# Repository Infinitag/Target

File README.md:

# Infinitag Target
[![CC BY-NC-SA 4.0][cc-by-nc-sa-shield]][cc-by-nc-sa] 

The Infinitag Target is a hit target for the Infinitag system based on an ESP32 S3 module. 
The target has the following functions:

- 12 individually controllable RGBW LEDs on the front for a status display.
- IR receivers to receive the signals
- One switchable 5V connector
- One switchable 3.3V connector
- One switches to pass the incoming signal
- Power supply port
- Extension port for additional external LEDs

## Software

In the "ArduinoCode" directory is the source code as .ino file for the Arduino IDE to upload to the taget board.

### Preparation

In order for the board to be recorded successfully, you must first add another source in the settings for the board management:

```
https://dl.espressif.com/dl/package_esp32_index.json
```

The board uses the CP2102N chipset to program the ESP32.
Please check in your device management if you have installed an appropriate driver on your device.
If not, install the appropriate driver, so that the Arduino IDE recognizes the target board.

### Settings

The following must be selected as the board for the upload:
ESP32 Arduino > ESP32 S3 Dev Module

### Libraries

- esp32 by Espressif Systems v 2.0.11 (3.0.0 not working with IRremote)
- IRremote by shirriff v 4.2.0

## Hardware

### PCB

We have published all files for the PCB incl. schematic, PCB design and BOM here:

https://oshwlab.com/crusher/infinitag-target

### 3D files

The files for a 3D enclosure can be found in the folder "Hardware/3DFiles".

Additionally you can find the latest version under the following link:

https://a360.co/3NOv182

## License
This work is licensed under a
[Creative Commons Attribution-NonCommercial-ShareAlike 4.0 International License][cc-by-nc-sa].

[![CC BY-NC-SA 4.0][cc-by-nc-sa-image]][cc-by-nc-sa]

[cc-by-nc-sa]: http://creativecommons.org/licenses/by-nc-sa/4.0/
[cc-by-nc-sa-image]: https://licensebuttons.net/l/by-nc-sa/4.0/88x31.png
[cc-by-nc-sa-shield]: https://img.shields.io/badge/License-CC%20BY--NC--SA%204.0-lightgrey.svg

## Additional

For more information about the Infinitag System please visit [infinitag.io](http://www.infinitag.io).

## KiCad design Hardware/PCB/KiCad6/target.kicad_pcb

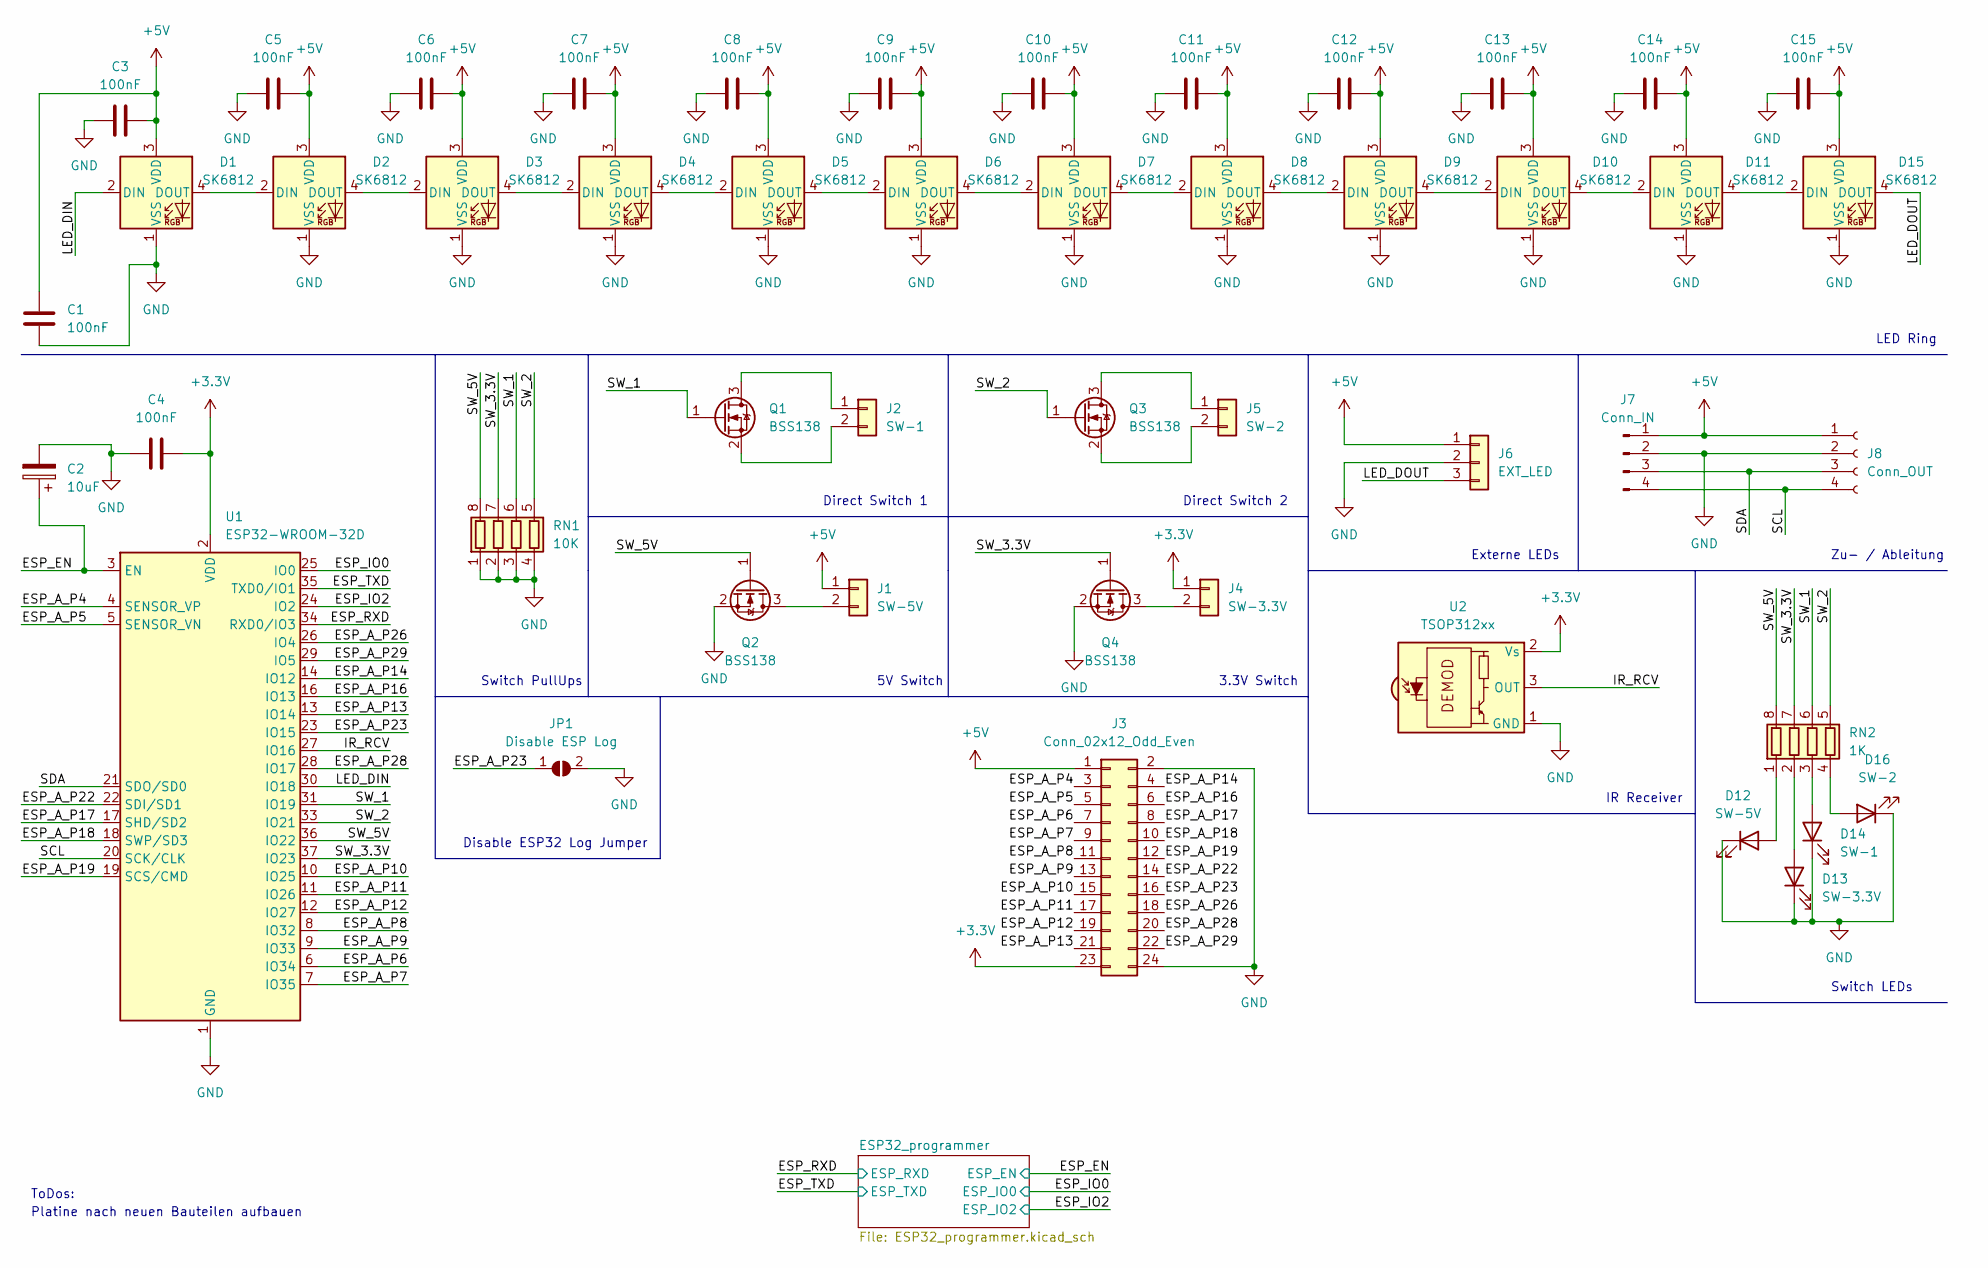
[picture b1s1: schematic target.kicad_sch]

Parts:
C1, C3, C4, C5, C6, C7, C8, C9, C10, C11, C12, C13, C14, C15: 100nF; C_0805_2012Metric_Pad1.18x1.45mm_HandSolder; LCSC C49678
C2: 10uF; CP_EIA-2012-12_Kemet-R_Pad1.30x1.05mm_HandSolder; LCSC C2976905
D1, D2, D3, D4, D5, D6, D7, D8, D9, D10, D11, D15: SK6812; LED_SK6812_PLCC4_5.0x5.0mm_P3.2mm; LCSC C5160656
D12: SW-5V; LED_1206_3216Metric_Pad1.42x1.75mm_HandSolder; LCSC C93094
D13: SW-3.3V; LED_1206_3216Metric_Pad1.42x1.75mm_HandSolder; LCSC C93094
D14: SW-1; LED_1206_3216Metric_Pad1.42x1.75mm_HandSolder; LCSC C93094
D16: SW-2; LED_1206_3216Metric_Pad1.42x1.75mm_HandSolder; LCSC C93094
J1: SW-5V; JST_PH_S2B-PH-K_1x02_P2.00mm_Horizontal; LCSC C173752
J2: SW-1; JST_PH_S2B-PH-K_1x02_P2.00mm_Horizontal; LCSC C173752
J3: Conn_02x12_Odd_Even; PinHeader_2x12_P2.54mm_Vertical; LCSC C62744
J4: SW-3.3V; JST_PH_S2B-PH-K_1x02_P2.00mm_Horizontal; LCSC C173752
J5: SW-2; JST_PH_S2B-PH-K_1x02_P2.00mm_Horizontal; LCSC C173752
J6: EXT_LED; JST_PH_S3B-PH-K_1x03_P2.00mm_Horizontal; LCSC C157929
J7: Conn_IN; JST_PH_S4B-PH-K_1x04_P2.00mm_Horizontal; LCSC C157926
J8: Conn_OUT; JST_PH_S4B-PH-K_1x04_P2.00mm_Horizontal; LCSC C157926
JP1: Disable ESP Log; SolderJumper-2_P1.3mm_Open_RoundedPad1.0x1.5mm
Q1, Q2, Q3, Q4: BSS138; SOT-23; LCSC C255592
RN1: 10K; R_Array_Convex_4x0603; LCSC C29718
RN2: 1K; R_Array_Convex_4x0603; LCSC C20197
U1: ESP32-WROOM-32D; ESP32-WROOM-32; LCSC C529578
U2: TSOP312xx; Vishay_CAST-3Pin

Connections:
+3V3: C4.2, J3.23, J4.1, U1.2 (VDD), U2.2 (Vs); also elsewhere on the board
+5V: C1.2, C3.2, C5.2, C6.2, C7.2, C8.2, C9.2, C10.2, C11.2, C12.2, C13.2, C14.2, C15.2, D1.3 (VDD), D2.3 (VDD), D3.3 (VDD), D4.3 (VDD), D5.3 (VDD), D6.3 (VDD), D7.3 (VDD), D8.3 (VDD), D9.3 (VDD), D10.3 (VDD), D11.3 (VDD), D15.3 (VDD), J1.1, J3.1, J6.1, J7.1, J8.1; also elsewhere on the board
/ESP_A_P4: J3.3, U1.4 (SENSOR_VP)
/ESP_A_P5: J3.5, U1.5 (SENSOR_VN)
/ESP_A_P6: J3.7, U1.6 (IO34)
/ESP_A_P7: J3.9, U1.7 (IO35)
/ESP_A_P8: J3.11, U1.8 (IO32)
/ESP_A_P9: J3.13, U1.9 (IO33)
/ESP_A_P10: J3.15, U1.10 (IO25)
/ESP_A_P11: J3.17, U1.11 (IO26)
/ESP_A_P12: J3.19, U1.12 (IO27)
/ESP_A_P13: J3.21, U1.13 (IO14)
/ESP_A_P14: J3.4, U1.14 (IO12)
/ESP_A_P16: J3.6, U1.16 (IO13)
/ESP_A_P17: J3.8, U1.17 (SHD/SD2)
/ESP_A_P18: J3.10, U1.18 (SWP/SD3)
/ESP_A_P19: J3.12, U1.19 (SCS/CMD)
/ESP_A_P22: J3.14, U1.22 (SDI/SD1)
/ESP_A_P23: J3.16, JP1.1 (A), U1.23 (IO15)
/ESP_A_P26: J3.18, U1.26 (IO4)
/ESP_A_P28: J3.20, U1.28 (IO17)
/ESP_A_P29: J3.22, U1.29 (IO5)
/ESP_EN: C2.1, U1.3 (EN); also elsewhere on the board
/ESP_IO0: U1.25 (IO0); also elsewhere on the board
/ESP_IO2: U1.24 (IO2); also elsewhere on the board
/ESP_RXD: U1.34 (RXD0/IO3); also elsewhere on the board
/ESP_TXD: U1.35 (TXD0/IO1); also elsewhere on the board
/IR_RCV: U1.27 (IO16), U2.3 (OUT)
/LED_DIN: D1.2 (DIN), U1.30 (IO18)
/LED_DOUT: D15.4 (DOUT), J6.3
/SCL: J7.4, J8.4, U1.20 (SCK/CLK)
/SDA: J7.3, J8.3, U1.21 (SDO/SD0)
/SW_1: Q1.1 (G), RN1.6 (R3.2), RN2.6 (R3.2), U1.31 (IO19)
/SW_2: Q3.1 (G), RN1.5 (R4.2), RN2.5 (R4.2), U1.33 (IO21)
/SW_3.3V: Q4.1 (G), RN1.7 (R2.2), RN2.7 (R2.2), U1.37 (IO23)
/SW_5V: Q2.1 (G), RN1.8 (R1.2), RN2.8 (R1.2), U1.36 (IO22)
GND: C1.1, C2.2, C3.1, C4.1, C5.1, C6.1, C7.1, C8.1, C9.1, C10.1, C11.1, C12.1, C13.1, C14.1, C15.1, D1.1 (VSS), D2.1 (VSS), D3.1 (VSS), D4.1 (VSS), D5.1 (VSS), D6.1 (VSS), D7.1 (VSS), D8.1 (VSS), D9.1 (VSS), D10.1 (VSS), D11.1 (VSS), D12.1 (K), D13.1 (K), D14.1 (K), D15.1 (VSS), D16.1 (K), J3.2, J3.24, J6.2, J7.2, J8.2, JP1.2 (B), Q2.2 (S), Q4.2 (S), RN1.1 (R1.1), RN1.2 (R2.1), RN1.3 (R3.1), RN1.4 (R4.1), U1.1 (GND), U1.15 (GND), U1.38 (GND), U1.39 (GND), U2.1 (GND); also elsewhere on the board
unnamed: D1.4 (DOUT), D2.2 (DIN)
unnamed: D2.4 (DOUT), D3.2 (DIN)
unnamed: D3.4 (DOUT), D4.2 (DIN)
unnamed: D4.4 (DOUT), D5.2 (DIN)
unnamed: D5.4 (DOUT), D6.2 (DIN)
unnamed: D6.4 (DOUT), D7.2 (DIN)
unnamed: D7.4 (DOUT), D8.2 (DIN)
unnamed: D8.4 (DOUT), D9.2 (DIN)
unnamed: D9.4 (DOUT), D10.2 (DIN)
unnamed: D10.4 (DOUT), D11.2 (DIN)
unnamed: D11.4 (DOUT), D15.2 (DIN)
unnamed: D12.2 (A), RN2.1 (R1.1)
unnamed: D13.2 (A), RN2.2 (R2.1)
unnamed: D14.2 (A), RN2.3 (R3.1)
unnamed: D16.2 (A), RN2.4 (R4.1)
unnamed: J1.2, Q2.3 (D)
unnamed: J2.1, Q1.3 (D)
unnamed: J2.2, Q1.2 (S)
unnamed: J4.2, Q4.3 (D)
unnamed: J5.1, Q3.3 (D)
unnamed: J5.2, Q3.2 (S)

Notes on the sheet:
IR Receiver
Switch LEDs
Zu- / Ableitung
ToDos:
5V Switch
LED Ring
Switch PullUps
3.3V Switch
Platine nach neuen Bauteilen aufbauen
Direct Switch 2
Externe LEDs
Direct Switch 1
Disable ESP32 Log Jumper

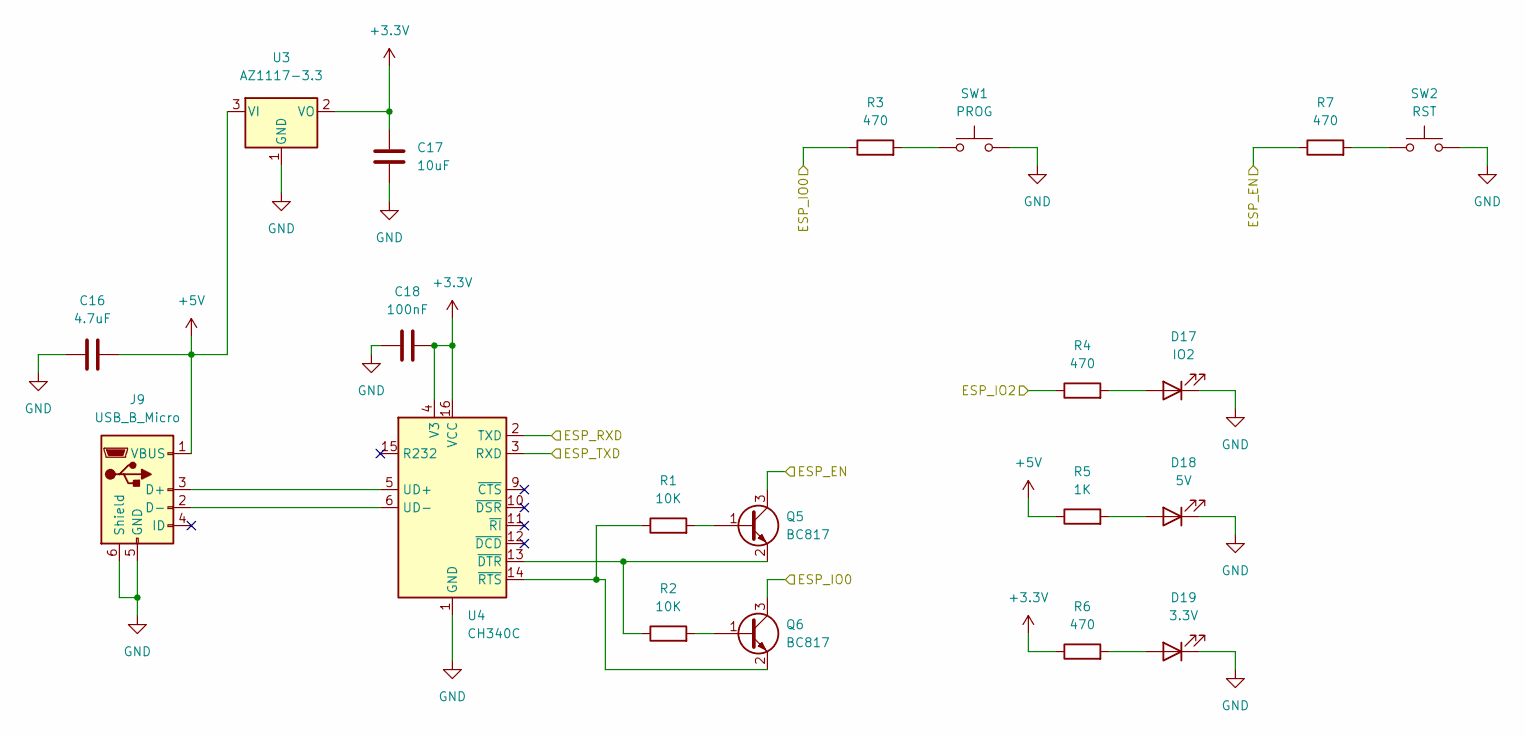
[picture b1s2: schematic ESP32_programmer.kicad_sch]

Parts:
C16: 4.7uF; C_0805_2012Metric_Pad1.18x1.45mm_HandSolder; LCSC C1779
C17: 10uF; C_0805_2012Metric_Pad1.18x1.45mm_HandSolder; LCSC C15850
C18: 100nF; C_0805_2012Metric_Pad1.18x1.45mm_HandSolder; LCSC C49678
D17: IO2; D_1206_3216Metric_Pad1.42x1.75mm_HandSolder; LCSC C88326
D18: 5V; D_1206_3216Metric_Pad1.42x1.75mm_HandSolder; LCSC C99881
D19: 3.3V; D_1206_3216Metric_Pad1.42x1.75mm_HandSolder; LCSC C99881
J9: USB_B_Micro; USB_Micro-B_Amphenol_10118194_Horizontal; LCSC C132563
Q5, Q6: BC817; SOT-23; LCSC C52801
R1, R2: 10K; R_0805_2012Metric_Pad1.20x1.40mm_HandSolder; LCSC C17414
R3, R4, R6, R7: 470; R_0805_2012Metric_Pad1.20x1.40mm_HandSolder; LCSC C17710
R5: 1K; R_0805_2012Metric_Pad1.20x1.40mm_HandSolder; LCSC C17513
SW1: PROG; SW_Push_1P1T_NO_6x6mm_H9.5mm; LCSC C83206
SW2: RST; SW_Push_1P1T_NO_6x6mm_H9.5mm; LCSC C83206
U3: AZ1117-3.3; SOT-223; LCSC C92517
U4: CH340C; SOIC-16_3.9x9.9mm_P1.27mm; LCSC C84681

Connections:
+3V3: C17.2, C18.2, R6.1, U3.2 (VO), U4.4 (V3), U4.16 (VCC); also elsewhere on the board
+5V: C16.2, J9.1 (VBUS), R5.1, U3.3 (VI); also elsewhere on the board
/ESP_EN: Q5.3 (C), R7.1; also elsewhere on the board
/ESP_IO0: Q6.3 (C), R3.1; also elsewhere on the board
/ESP_IO2: R4.1; also elsewhere on the board
/ESP_RXD: U4.2 (TXD); also elsewhere on the board
/ESP_TXD: U4.3 (RXD); also elsewhere on the board
GND: C16.1, C17.1, C18.1, D17.1 (K), D18.1 (K), D19.1 (K), J9.5 (GND), J9.6 (Shield), SW1.2, SW2.2, U3.1 (GND), U4.1 (GND); also elsewhere on the board
unnamed: D17.2 (A), R4.2
unnamed: D18.2 (A), R5.2
unnamed: D19.2 (A), R6.2
unnamed: J9.2 (D-), U4.6 (UD-)
unnamed: J9.3 (D+), U4.5 (UD+)
unnamed: Q5.1 (B), R1.2
unnamed: Q5.2 (E), R2.1, U4.13 (~DTR)
unnamed: Q6.1 (B), R2.2
unnamed: Q6.2 (E), R1.1, U4.14 (~RTS)
unnamed: R3.2, SW1.1
unnamed: R7.2, SW2.1

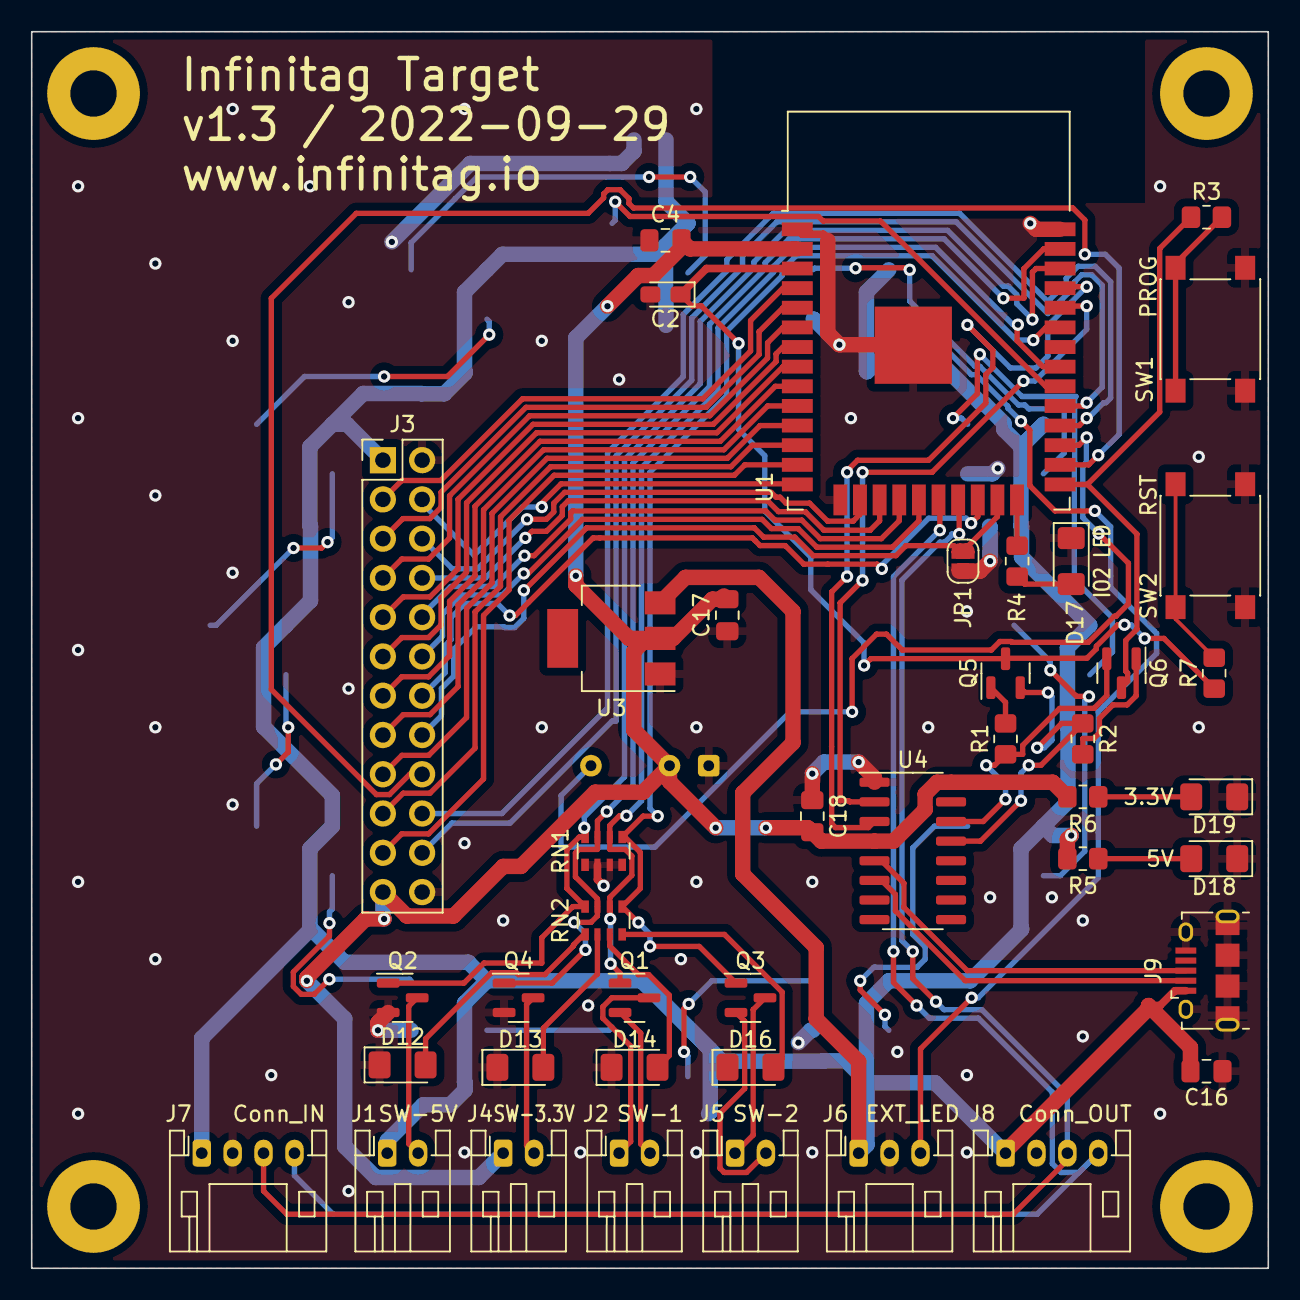
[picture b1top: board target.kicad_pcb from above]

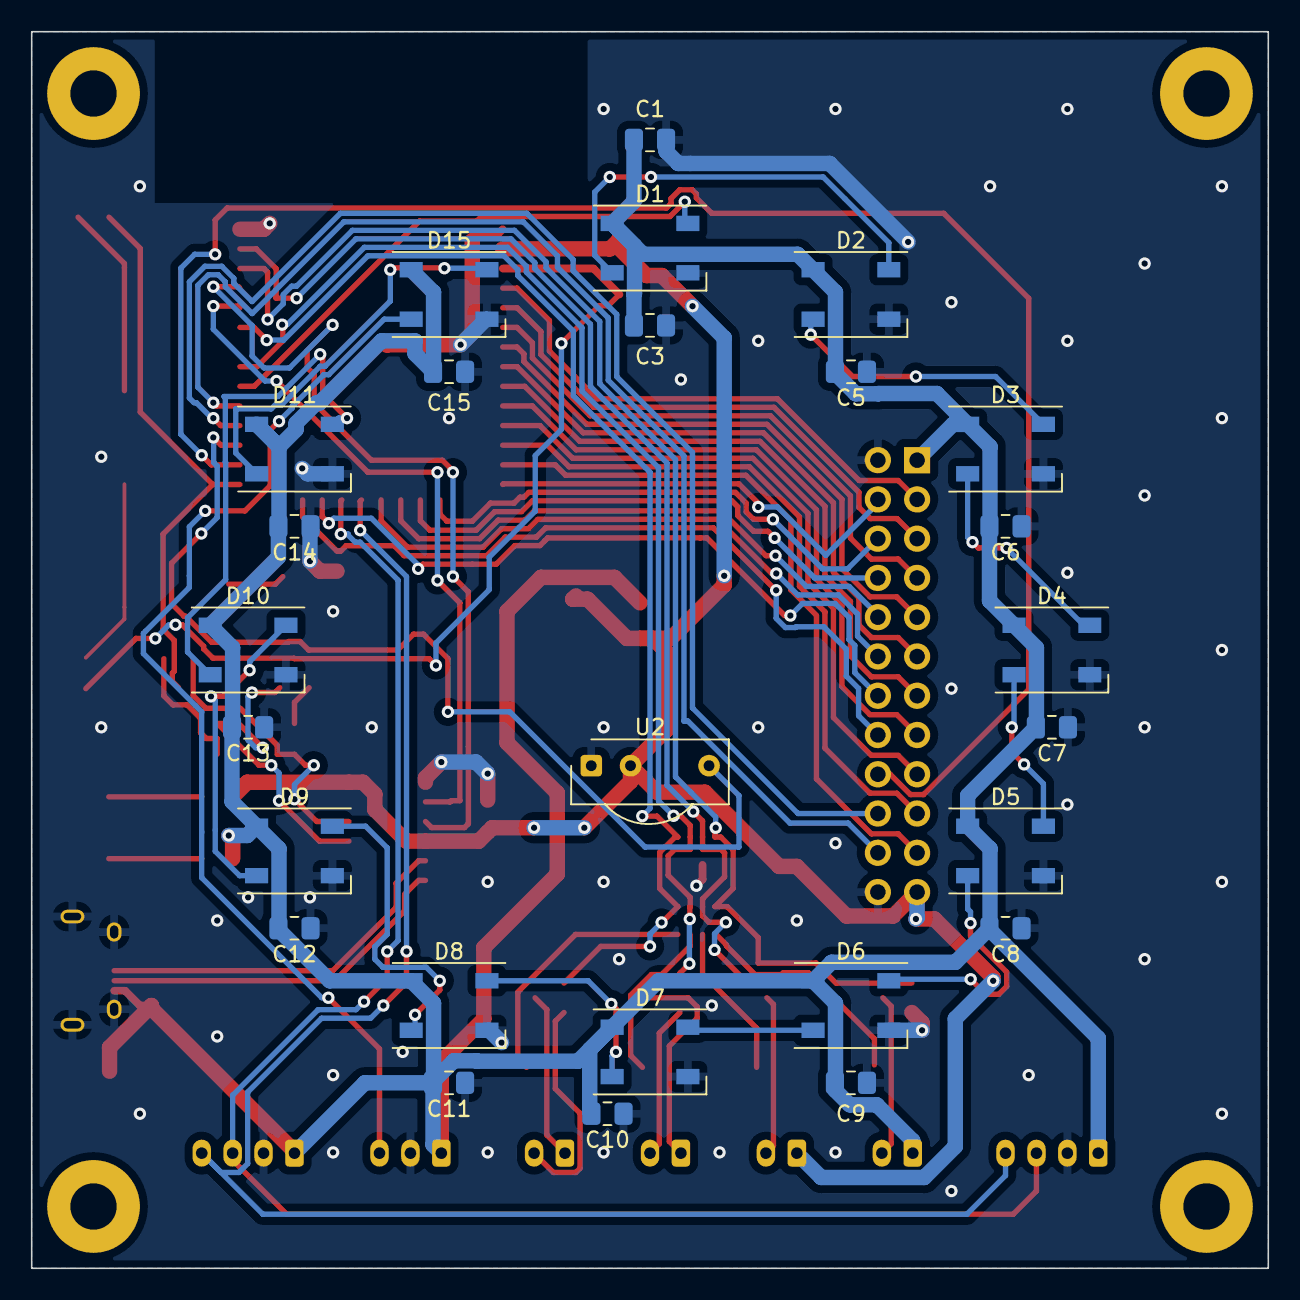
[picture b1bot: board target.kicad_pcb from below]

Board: 2 copper layers, 80.0 x 80.0 mm, 68 parts (26 on the bottom side), 69 nets.

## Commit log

2022-09-25 Current Version
2022-09-25 Code in separate folder
2022-09-25 KiCad6 PCB Project
2022-09-25 Files for JLCPCB
2022-09-25 Correct folder structure for Arduino IDE + update Readme
2022-09-25 Update license info
2022-09-25 Update correct license text
2022-09-25 Update correct license
2022-09-28 PCB Update from current schema
2022-09-28 Add gitignore for backups
2022-09-28 Remove backups
2022-09-29 Remove existing Backups
2022-09-29 PCB files with current changes updated
2023-07-16 Update target source code to v3.1.0
    Complete redesign with a esp32 S3 dual core chip + new PCB design and trigger four sound effects
2023-07-16 Last Update from v1
2023-07-16 Images for v3
2023-07-16 Remove old hardware files
2023-07-16 3D files for the case
2023-07-16 Update readme with 3d Files
2023-07-16 Add new build for esp32 s3
2023-07-18 Fix: Only to the action if target is not in hit mode
2023-07-18 Option to trigger config portal at runtime
2023-07-18 define pins according to the same pattern
2023-07-18 Correct version of the code (3.1 was version of the pcb)
2024-02-21 Replace webserver with MQTT
2024-02-22 Switch from Arduino IDE to VisualStudio Code with PlatformIO
2024-02-22 Add declarations
2024-02-22 fix wrong definitions
2024-02-22 update gitignore
2024-02-22 Add mqtt params in wifi manager
